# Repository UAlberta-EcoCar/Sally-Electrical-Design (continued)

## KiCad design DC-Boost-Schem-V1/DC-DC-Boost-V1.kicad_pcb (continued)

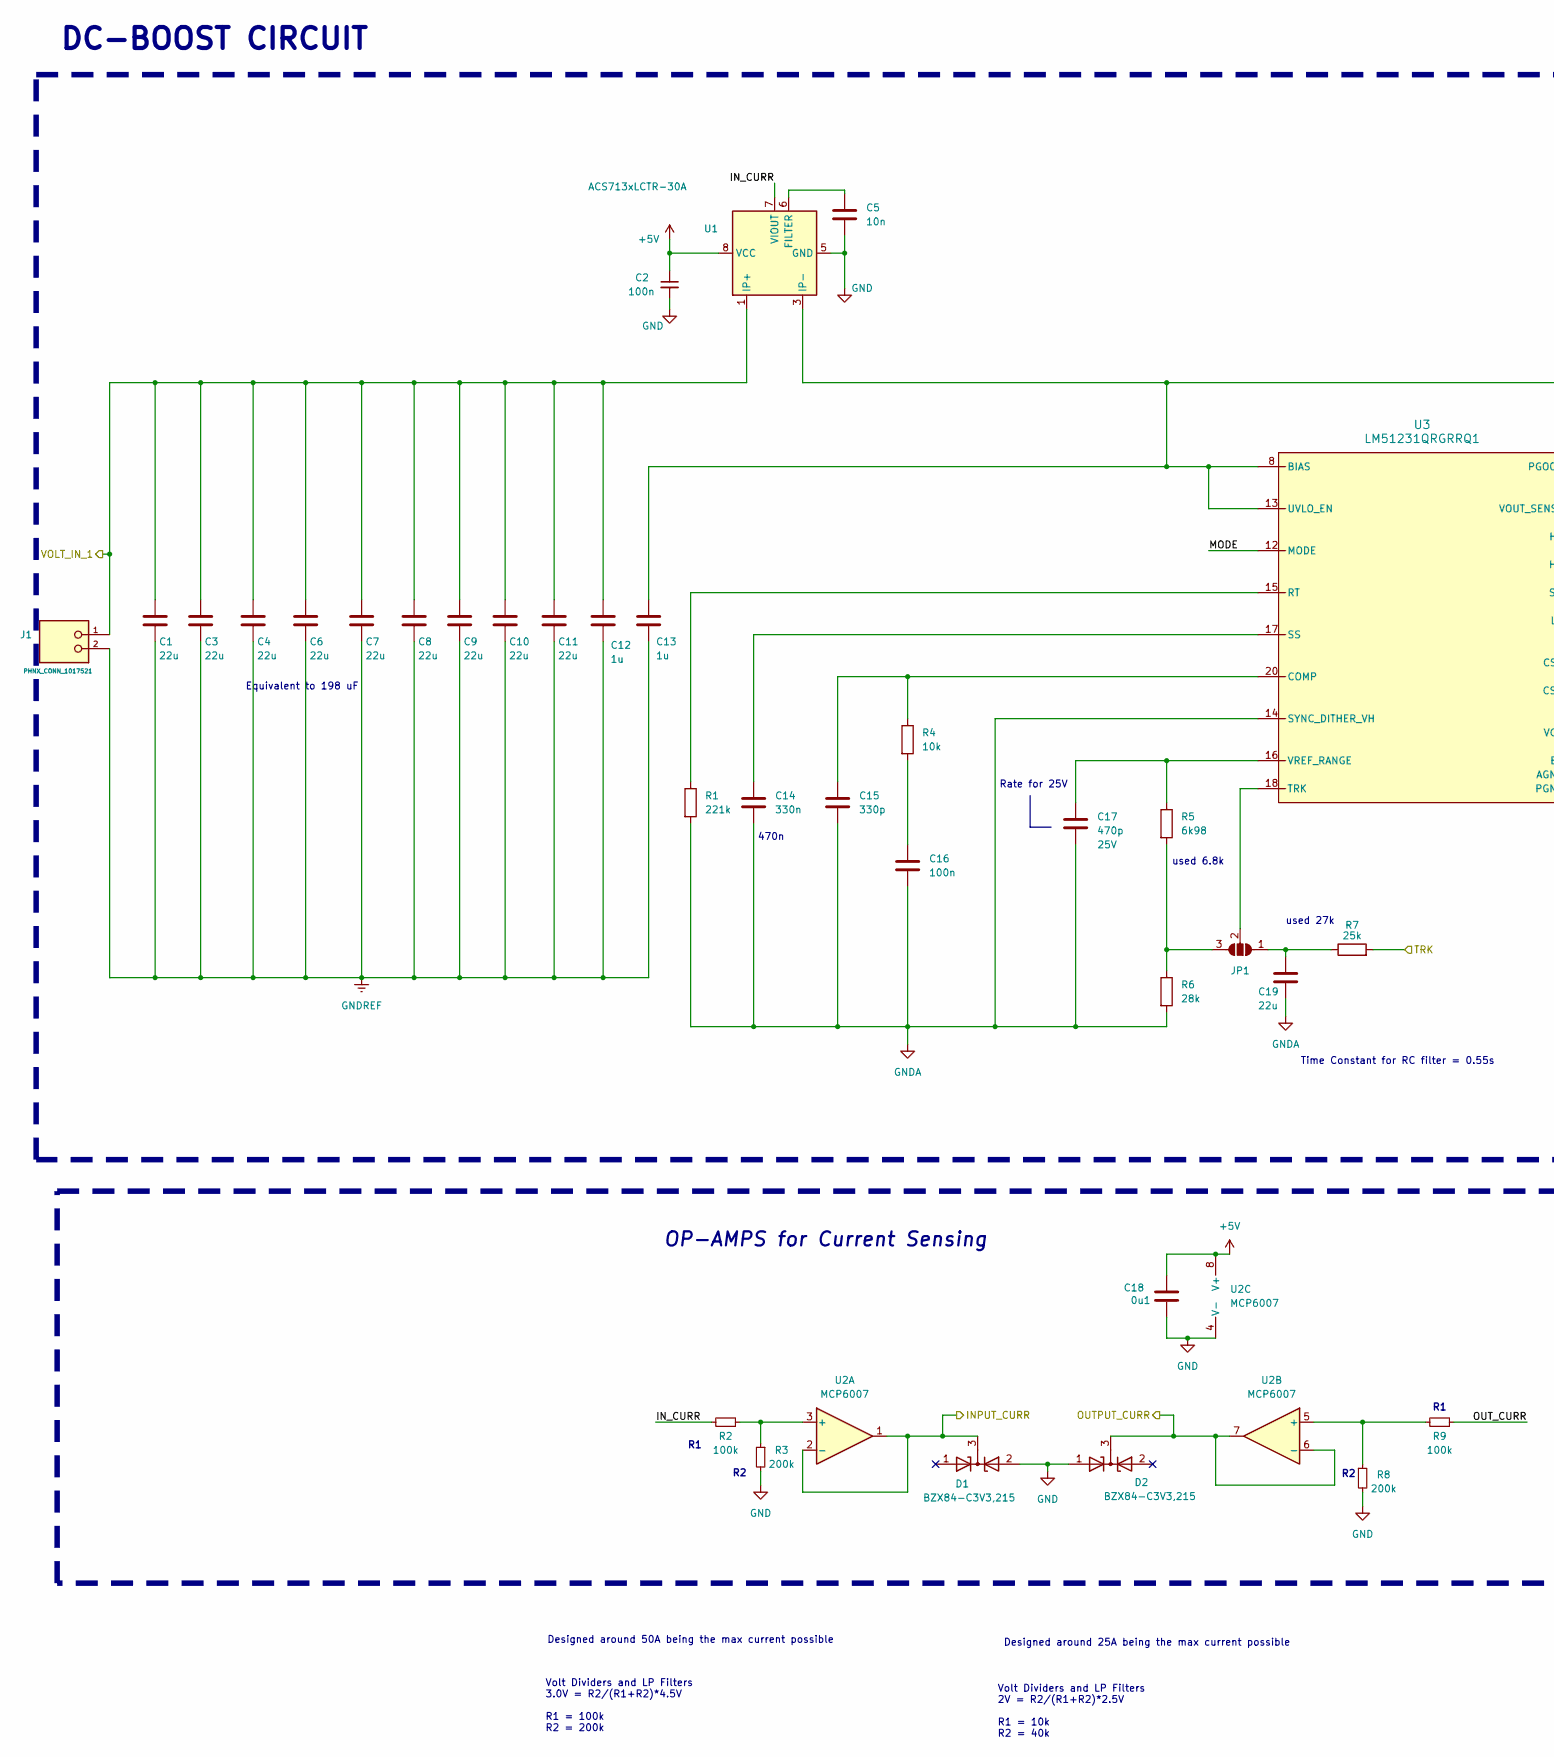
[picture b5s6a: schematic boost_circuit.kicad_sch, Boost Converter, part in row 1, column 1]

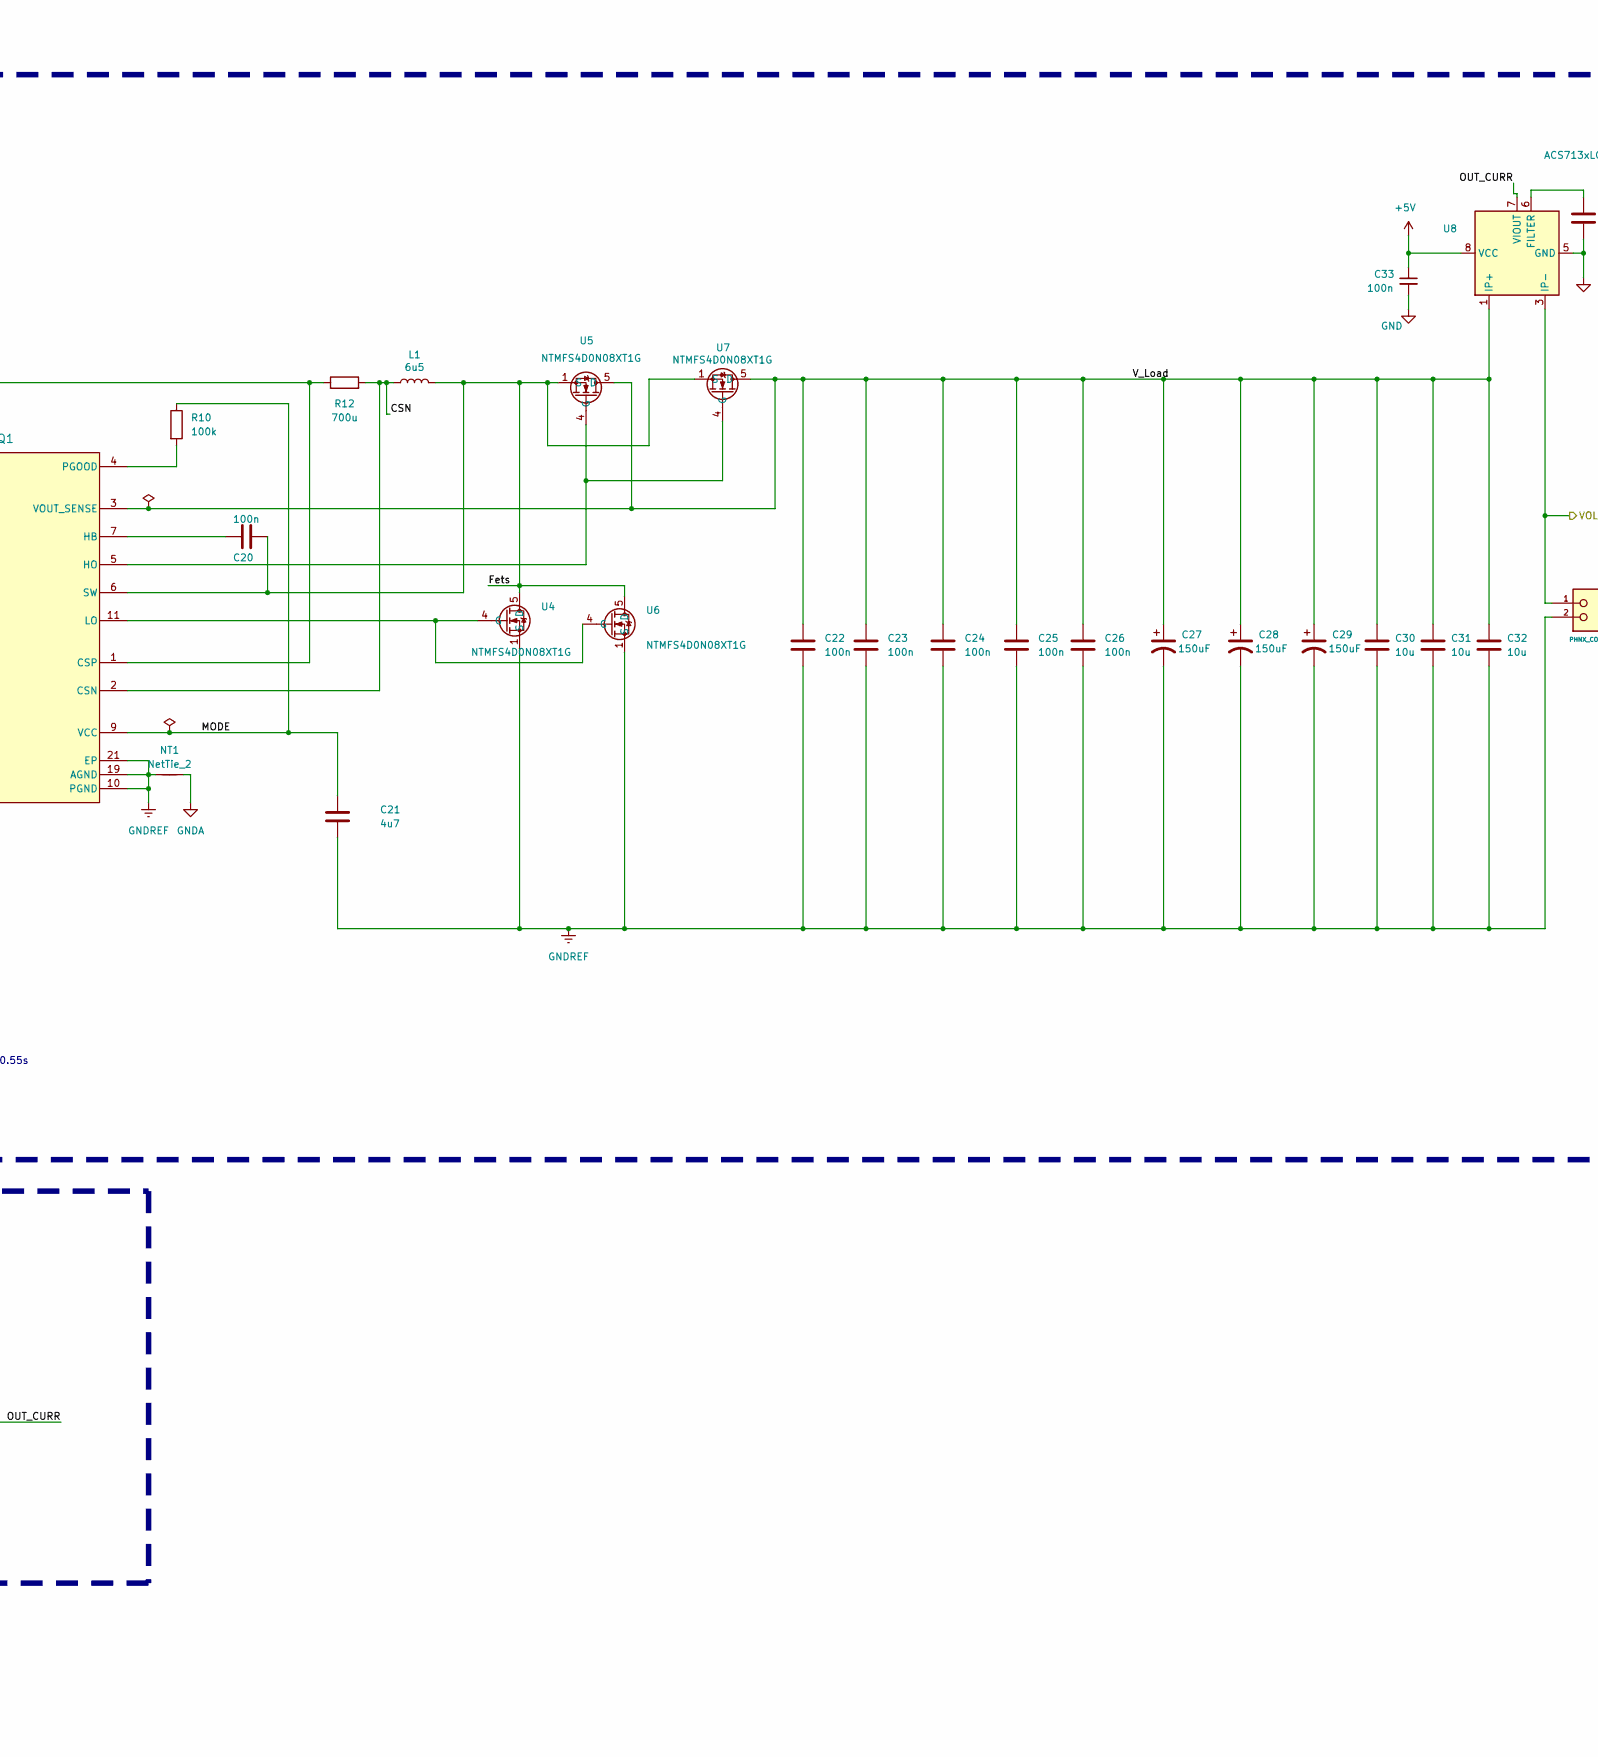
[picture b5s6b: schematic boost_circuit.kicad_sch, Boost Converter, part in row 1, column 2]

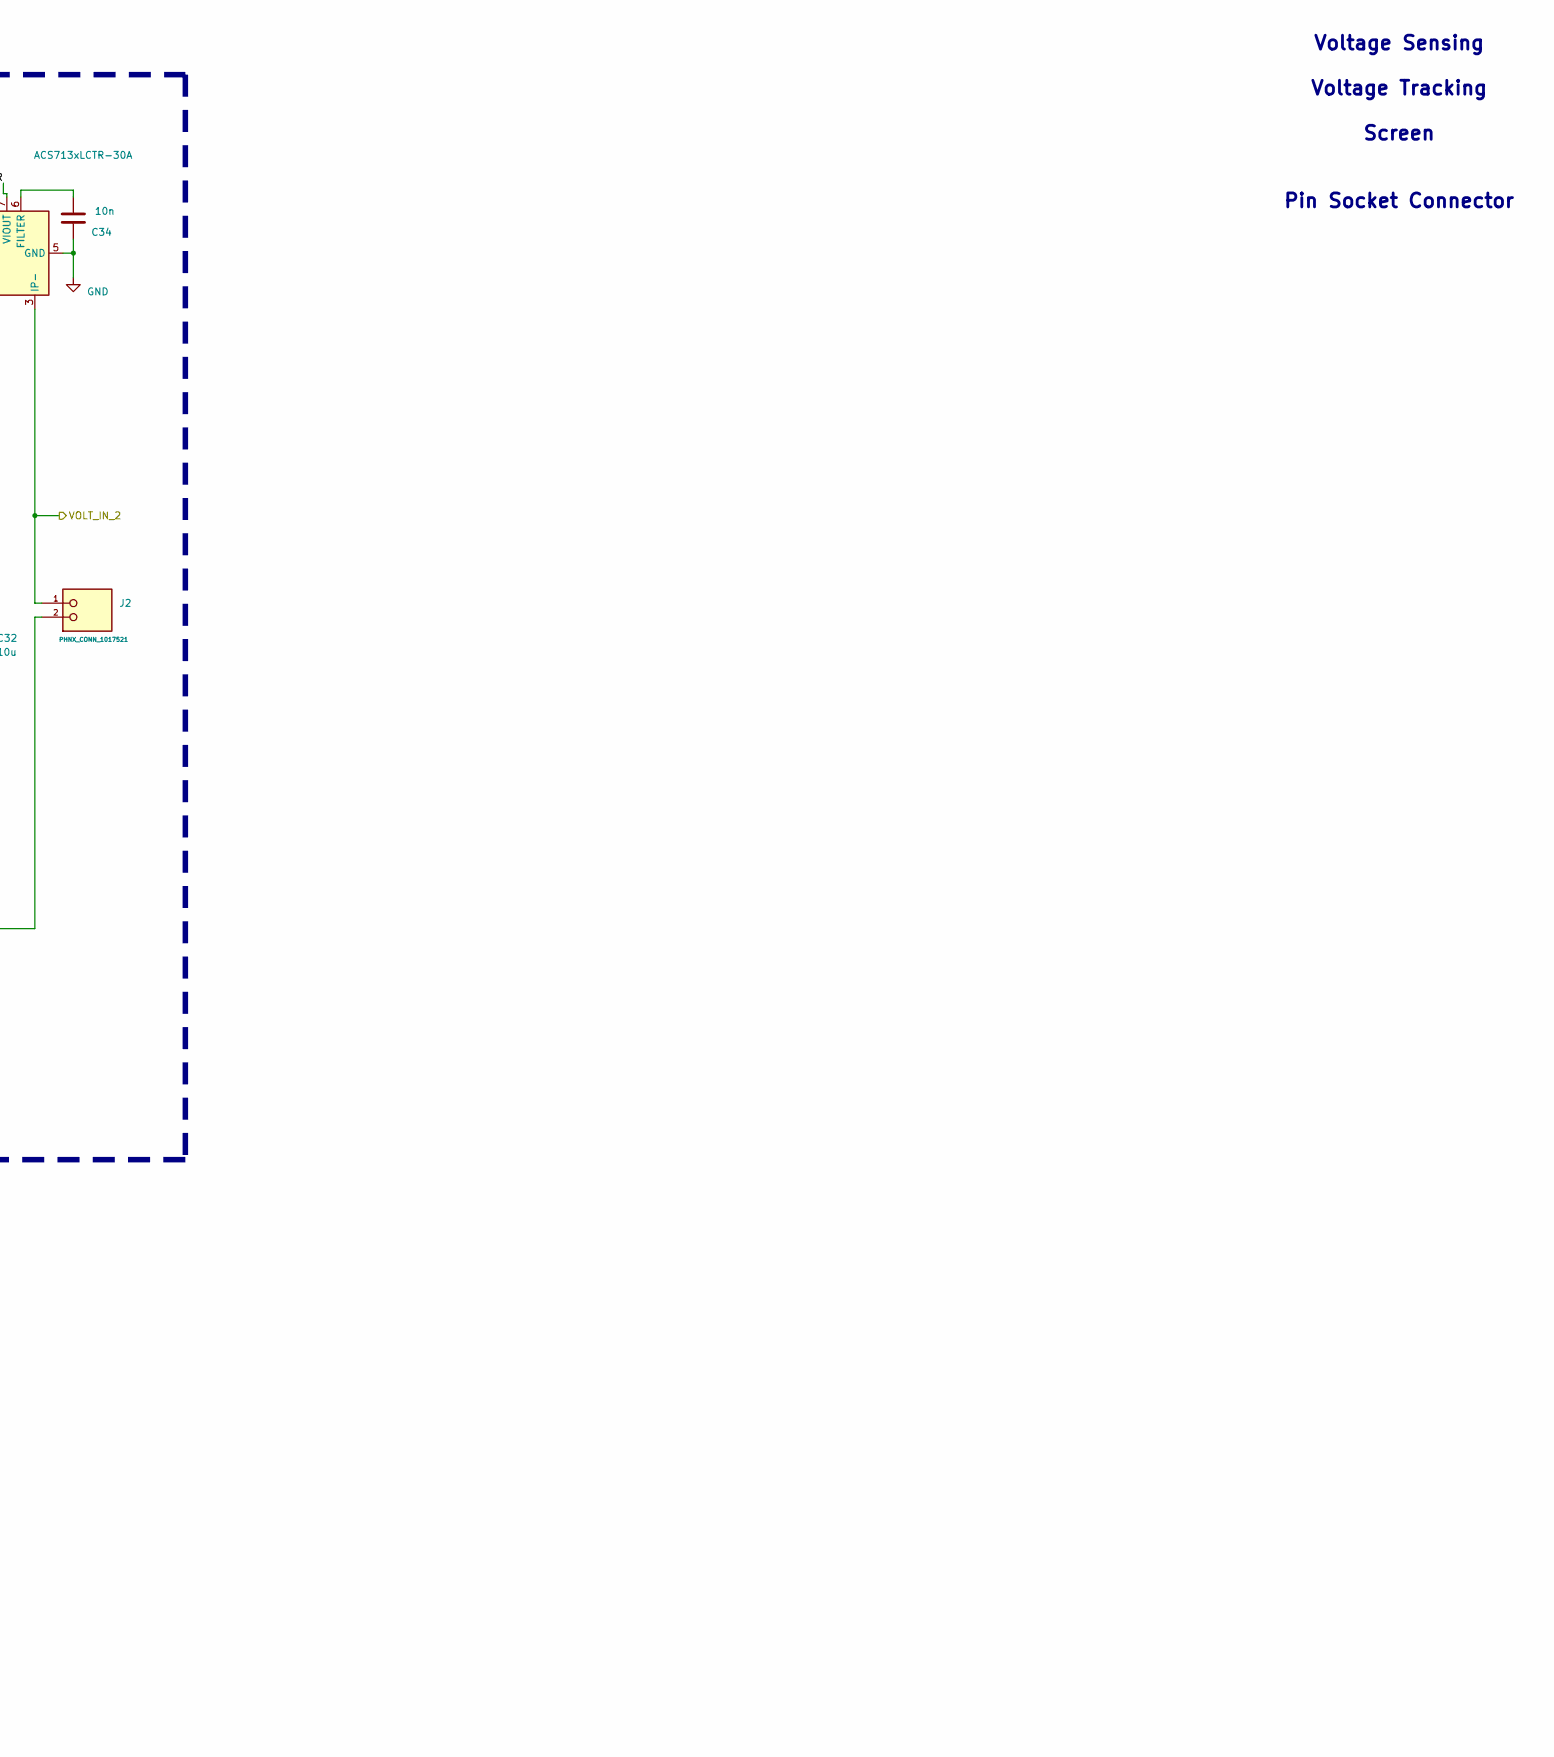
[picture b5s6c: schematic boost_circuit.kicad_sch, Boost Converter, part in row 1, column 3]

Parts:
C1, C3, C4, C6, C7, C8, C9, C10, C11: 22u; C_0805_2012Metric
C2, C33: 100n; C_0603_1608Metric; Part# C88219
C5, C34: 10n; C_0603_1608Metric_Pad1.08x0.95mm_HandSolder
C12, C13: 1u; C_0603_1608Metric
C14: 330n; C_0603_1608Metric
C15: 330p; C_0805_2012Metric
C16, C22, C23, C24, C25, C26: 100n; C_0603_1608Metric
C17: 470p; C_0603_1608Metric; Rating 25V
C18: 0u1; C_0603_1608Metric
C19: 22u; C_0603_1608Metric
C20: 100n; R_0603_1608Metric
C21: 4u7; C_0603_1608Metric
C27, C28, C29: 150uF; CAP_EEVFK1K151Q
C30, C31, C32: 10u; C_1210_3225Metric
D1, D2: BZX84-C3V3,215; SOT-23-3_Adjusted; Part# C85087
J1, J2: PHNX_CONN_1017521; PHOENIX_1017521; PARTREV 04.01.2018
JP1: SolderJumper_3_Open; SolderJumper-3_P1.3mm_Open_RoundedPad1.0x1.5mm
L1: 6u5; L_Bourns_SRR1208_12.7x12.7mm
NT1: NetTie_2; NetTie-2_SMD_Pad0.5mm
R1: 221k; R_0603_1608Metric
R2, R9, R10: 100k; R_0603_1608Metric
R3: 200k; R_0603_1608Metric; Part# C25811
R4: 10k; R_0603_1608Metric_Pad0.98x0.95mm_HandSolder
R5: 6k98; R_0603_1608Metric
R6: 28k; R_0603_1608Metric
R7: 25k; R_0603_1608Metric
R8: 200k; R_0603_1608Metric
R12: 700u; WSLP3921L7000FEA
U1, U8: ACS713xLCTR-30A; SOIC-8_3.9x4.9mm_P1.27mm
U2: MCP6007; SOIC-8_3.9x4.9mm_P1.27mm
U3: LM51231QRGRRQ1; RGR0020C-MFG
U4, U5, U6, U7: NTMFS4D0N08XT1G; PowerMosDFNHybrid

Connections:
+5V: C2.1, C18.1, C33.1, U1.8 (VCC), U2.8 (V+), U8.8 (VCC); also elsewhere on the board
/Boost-Circuit/CSN: L1.1, R12.2, U3.2 (CSN)
/Boost-Circuit/Fets: C20.1, L1.2, U3.6 (SW), U4.5 (D), U5.1 (S), U5.2 (S), U5.3 (S), U6.5 (D), U7.1 (S), U7.2 (S), U7.3 (S)
/Boost-Circuit/INPUT_CURR: D1.3 (K), U2.1, U2.2 (-); also elsewhere on the board
/Boost-Circuit/IN_CURR: R2.2, U1.7 (VIOUT)
/Boost-Circuit/MODE: C21.1, R10.1, U3.9 (VCC), U3.12 (MODE)
/Boost-Circuit/OUTPUT_CURR: D2.3 (K), U2.6 (-), U2.7; also elsewhere on the board
/Boost-Circuit/OUT_CURR: R9.1, U8.7 (VIOUT)
/Boost-Circuit/TRK: R7.2; also elsewhere on the board
/Boost-Circuit/VOLT_IN_1: C1.1, C3.1, C4.1, C6.1, C7.1, C8.1, C9.1, C10.1, C11.1, C12.1, J1.1, U1.1 (IP+), U1.2 (IP+); also elsewhere on the board
/Boost-Circuit/VOLT_IN_2: J2.1, U8.3 (IP-), U8.4 (IP-); also elsewhere on the board
/Boost-Circuit/V_Load: C22.1, C23.1, C24.1, C25.1, C26.1, C27.1, C28.1, C29.1, C30.1, C31.1, C32.1, U3.3 (VOUT_SENSE), U5.5 (D), U7.5 (D), U8.1 (IP+), U8.2 (IP+)
GND: C2.2, C5.1, C18.2, C33.2, C34.1, D1.2 (A), D2.1 (A), R3.2, R8.2, U1.5 (GND), U2.4 (V-), U8.5 (GND); also elsewhere on the board
GNDA: C14.2, C15.2, C16.2, C17.2, C19.2, NT1.2, R1.2, R6.2, U3.14 (SYNC_DITHER_VH)
GNDREF: C1.2, C3.2, C4.2, C6.2, C7.2, C8.2, C9.2, C10.2, C11.2, C12.2, C13.2, C21.2, C22.2, C23.2, C24.2, C25.2, C26.2, C27.2, C28.2, C29.2, C30.2, C31.2, C32.2, J1.2, J2.2, NT1.1, U3.10 (PGND), U3.19 (AGND), U3.21 (EP), U4.1 (S), U4.2 (S), U4.3 (S), U6.1 (S), U6.2 (S), U6.3 (S); also elsewhere on the board
unnamed: C16.1, R4.2
unnamed: C19.1, JP1.1 (A), R7.1
unnamed: JP1.3 (B), R5.2, R6.1
unnamed: JP1.2 (C), U3.18 (TRK)
unnamed: C5.2, U1.6 (FILTER)
unnamed: R2.1, R3.1, U2.3 (+)
unnamed: R8.1, R9.2, U2.5 (+)
unnamed: C13.1, R12.1, U1.3 (IP-), U1.4 (IP-), U3.1 (CSP), U3.8 (BIAS), U3.13 (UVLO_EN)
unnamed: C15.1, R4.1, U3.20 (COMP)
unnamed: C20.2, U3.7 (HB)
unnamed: U3.5 (HO), U5.4 (G), U7.4 (G)
unnamed: U3.11 (LO), U4.4 (G), U6.4 (G)
unnamed: R10.2, U3.4 (PGOOD)
unnamed: R1.1, U3.15 (RT)
unnamed: C14.1, U3.17 (SS)
unnamed: C17.1, R5.1, U3.16 (VREF_RANGE)
unnamed: C34.2, U8.6 (FILTER)

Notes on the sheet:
used 27k
DC-BOOST CIRCUIT
470n
used 6.8k
Volt Dividers and LP Filters 3.0V = R2/(R1+R2)*4.5V R1 = 100k R2 = 200k
Time Constant for RC filter = 0.55s
Volt Dividers and LP Filters 2V = R2/(R1+R2)*2.5V R1 = 10k R2 = 40k
OP-AMPS for Current Sensing
Voltage Sensing Voltage Tracking Screen Pin Socket Connector
Designed around 25A being the max current possible
Rate for 25V
Designed around 50A being the max current possible
Equivalent to 198 uF

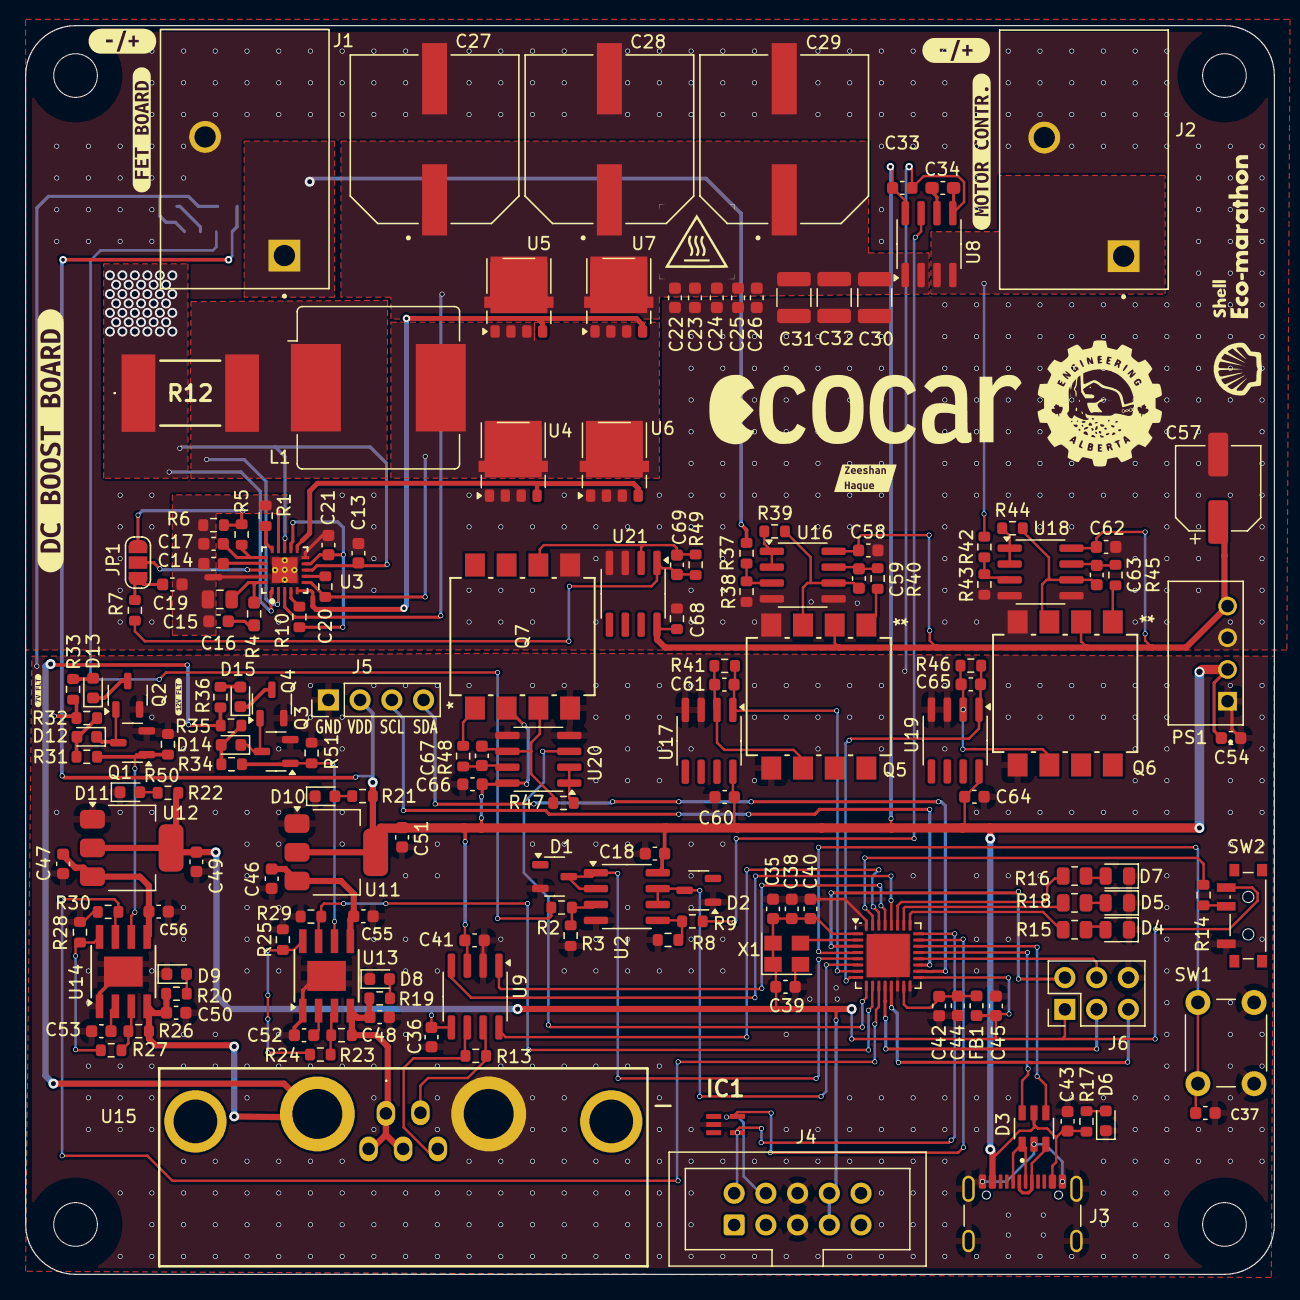
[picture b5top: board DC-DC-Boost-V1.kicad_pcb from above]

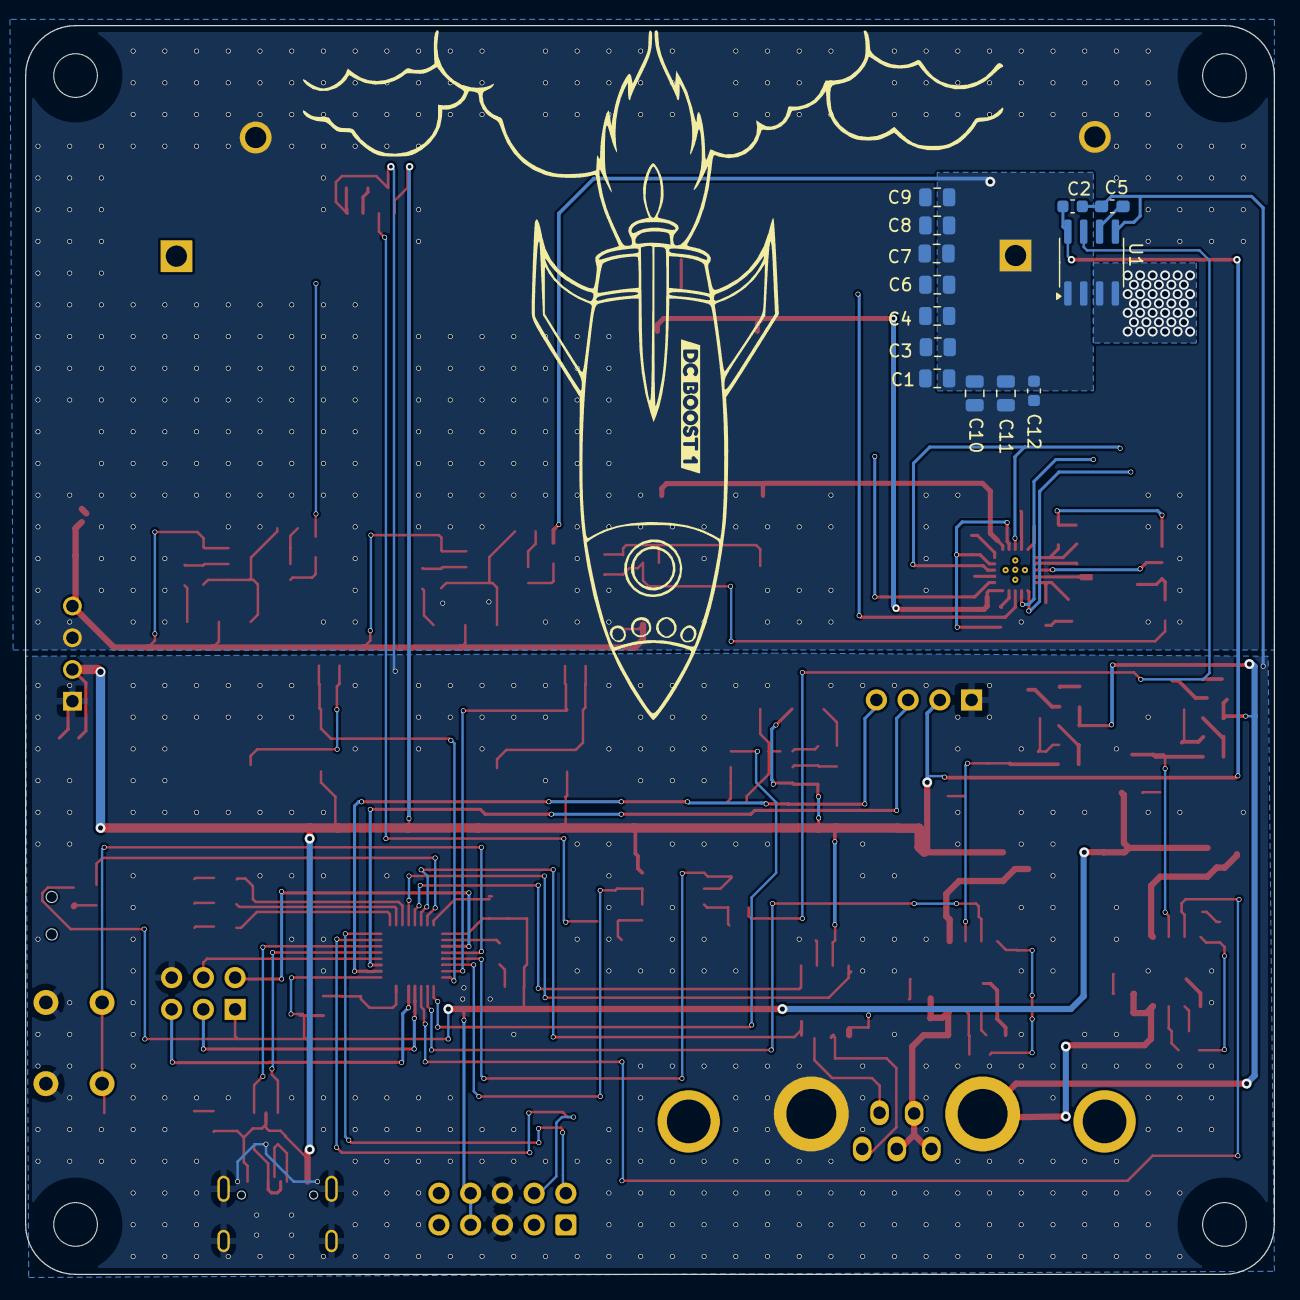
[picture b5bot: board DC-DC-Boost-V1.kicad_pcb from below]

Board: 2 copper layers, 100.0 x 100.0 mm, 190 parts (14 on the bottom side), 109 nets.

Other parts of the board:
D14: Green; LED_0603_1608Metric
D15: Red; LED_0603_1608Metric
kibuzzard-677F2B69: G***; kibuzzard-677F2B69
kibuzzard-677F2E47: G***; kibuzzard-677F2E47
kibuzzard-6743FE0A: G***; kibuzzard-6743FE0A
kibuzzard-6743FE6D: G***; kibuzzard-6743FE6D
kibuzzard-6743FE8B: G***; kibuzzard-6743FE8B
kibuzzard-6778B2B5: G***; kibuzzard-6778B2B5
kibuzzard-6778B2CF: G***; kibuzzard-6778B2CF
kibuzzard-67392652, kibuzzard-67392652#2: G***; kibuzzard-67392652

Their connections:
unnamed 69: D14.2 (A); also elsewhere on the board
unnamed 70: D14.1 (K); also elsewhere on the board
unnamed 71: D15.2 (A); also elsewhere on the board
unnamed 72: D15.1 (K); also elsewhere on the board

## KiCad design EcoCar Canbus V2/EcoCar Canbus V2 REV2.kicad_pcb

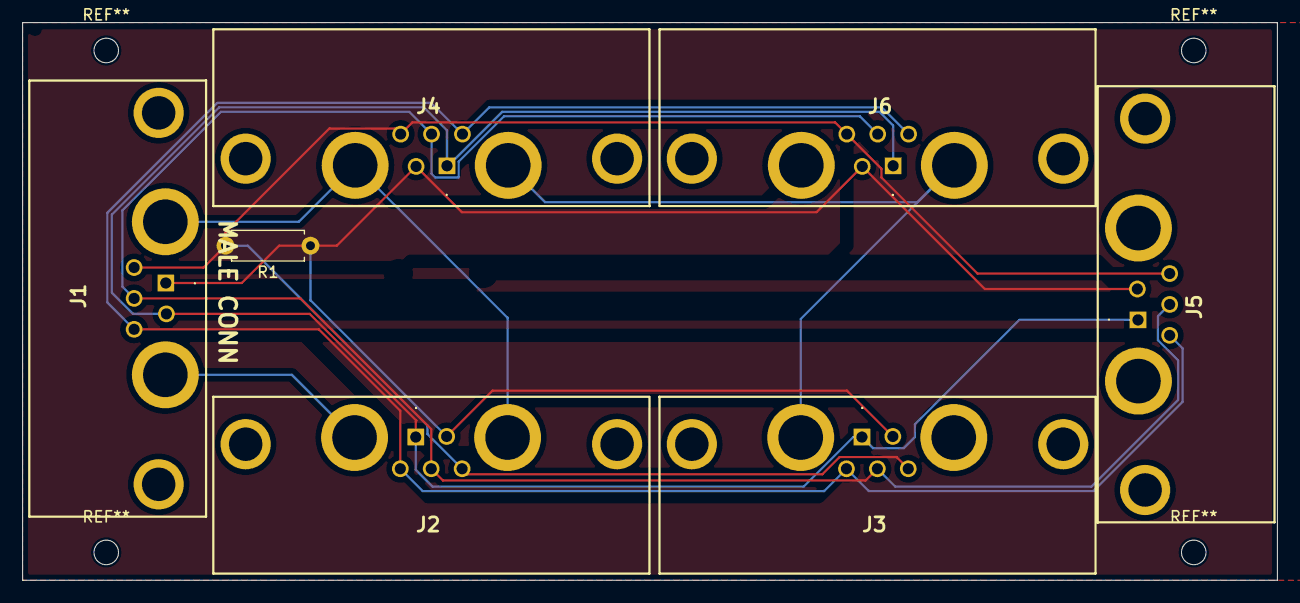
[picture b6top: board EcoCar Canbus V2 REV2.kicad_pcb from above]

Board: 2 copper layers, 112.5 x 50.0 mm, 7 parts (0 on the bottom side), 7 nets.

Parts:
J1, J2, J3, J4, J5, J6: DB7W2-30A
R1: 120; R_Axial_DIN0207_L6.3mm_D2.5mm_P7.62mm_Horizontal

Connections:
unnamed: J1.1, J2.2, J3.2, J4.2, J5.2, J6.2
unnamed: J1.2, J2.1, J3.1, J4.1, J5.1, J6.1
unnamed: J1.3, J2.5, J3.5, J4.5, J5.5, J6.5, R1.2
unnamed: J1.4, J2.4, J3.4, J4.4, J5.4, J6.4
unnamed: J1.5, J2.3, J3.3, J4.3, J5.3, J6.3
unnamed: J1.6, J2.7, J3.7, J4.7, J5.7, J6.7, R1.1
unnamed: J1.7, J2.6, J3.6, J4.6, J5.6, J6.6
